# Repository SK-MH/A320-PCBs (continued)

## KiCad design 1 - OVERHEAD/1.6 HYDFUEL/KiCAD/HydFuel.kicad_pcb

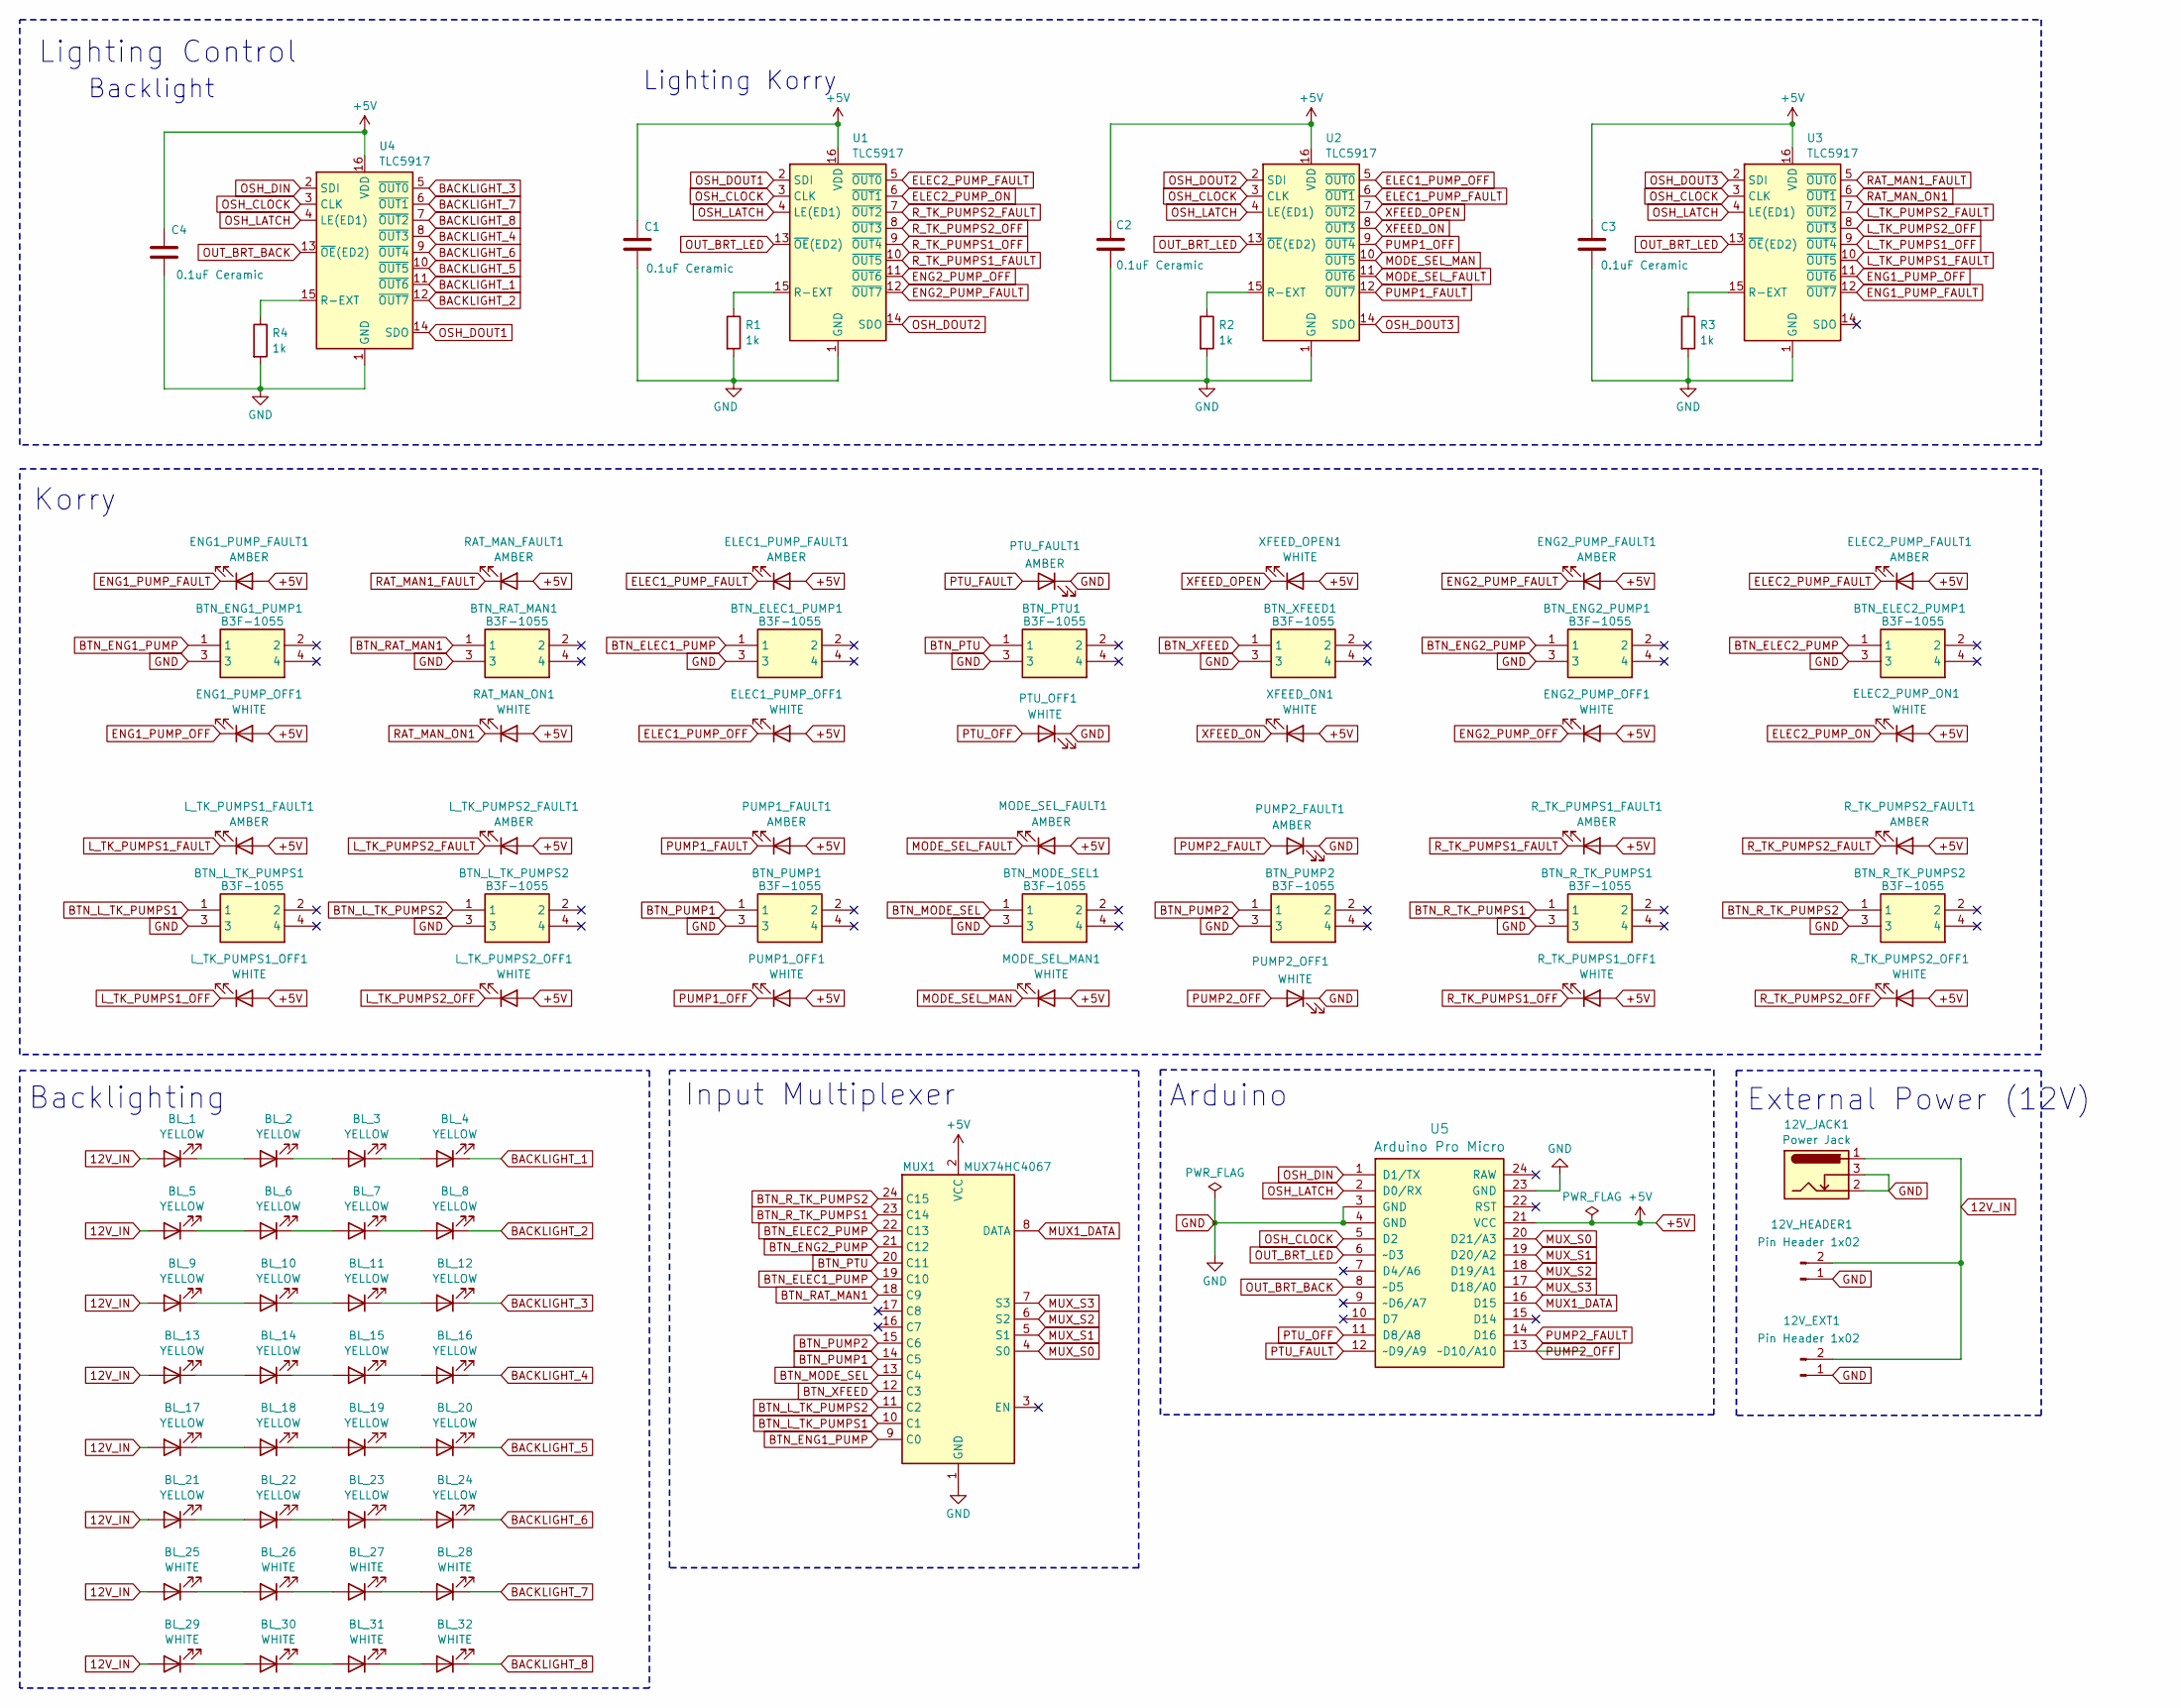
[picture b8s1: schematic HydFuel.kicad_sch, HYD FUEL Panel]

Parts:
12V_EXT1, 12V_HEADER1: Pin Header 1x02; JST_EH_B2B-EH-A_1x02_P2.50mm_Vertical
12V_JACK1: Power Jack; BarrelJack_Horizontal
BL_1, BL_2, BL_3, BL_4, BL_5, BL_6, BL_7, BL_8, BL_9, BL_10, BL_11, BL_12, BL_13, BL_14, BL_15, BL_16, BL_17, BL_18, BL_19, BL_20, BL_21, BL_22, BL_23, BL_24: YELLOW; LED_D3.0mm
BL_25, BL_26, BL_27, BL_28, BL_29, BL_30, BL_31, BL_32: WHITE; LED_D3.0mm
BTN_ELEC1_PUMP1, BTN_ELEC2_PUMP1: B3F-1055; B3F1000; Mouser Part Number 653-B3F-1055
BTN_ENG1_PUMP1, BTN_ENG2_PUMP1: B3F-1055; B3F1000; Mouser Part Number 653-B3F-1055
BTN_L_TK_PUMPS1, BTN_L_TK_PUMPS2: B3F-1055; B3F1000; Mouser Part Number 653-B3F-1055
BTN_MODE_SEL1: B3F-1055; B3F1000; Mouser Part Number 653-B3F-1055
BTN_PTU1: B3F-1055; B3F1000; Mouser Part Number 653-B3F-1055
BTN_PUMP1, BTN_PUMP2: B3F-1055; B3F1000; Mouser Part Number 653-B3F-1055
BTN_RAT_MAN1: B3F-1055; B3F1000; Mouser Part Number 653-B3F-1055
BTN_R_TK_PUMPS1, BTN_R_TK_PUMPS2: B3F-1055; B3F1000; Mouser Part Number 653-B3F-1055
BTN_XFEED1: B3F-1055; B3F1000; Mouser Part Number 653-B3F-1055
C1, C2, C3, C4: 0.1uF Ceramic; C_Disc_D3.0mm_W1.6mm_P2.50mm
ELEC1_PUMP_FAULT1, ELEC2_PUMP_FAULT1: AMBER; LED_D3.0mm
ELEC1_PUMP_OFF1, ELEC2_PUMP_ON1: WHITE; LED_D3.0mm
ENG1_PUMP_FAULT1, ENG2_PUMP_FAULT1: AMBER; LED_D3.0mm
ENG1_PUMP_OFF1, ENG2_PUMP_OFF1: WHITE; LED_D3.0mm
L_TK_PUMPS1_FAULT1, L_TK_PUMPS2_FAULT1: AMBER; LED_D3.0mm
L_TK_PUMPS1_OFF1, L_TK_PUMPS2_OFF1: WHITE; LED_D3.0mm
MODE_SEL_FAULT1: AMBER; LED_D3.0mm
MODE_SEL_MAN1: WHITE; LED_D3.0mm
MUX1: MUX74HC4067
PTU_FAULT1: AMBER; LED_D3.0mm
PTU_OFF1: WHITE; LED_D3.0mm
PUMP1_FAULT1, PUMP2_FAULT1: AMBER; LED_D3.0mm
PUMP1_OFF1, PUMP2_OFF1: WHITE; LED_D3.0mm
R1, R2, R3, R4: 1k; R_Axial_DIN0204_L3.6mm_D1.6mm_P7.62mm_Horizontal
RAT_MAN_FAULT1: AMBER; LED_D3.0mm
RAT_MAN_ON1: WHITE; LED_D3.0mm
R_TK_PUMPS1_FAULT1, R_TK_PUMPS2_FAULT1: AMBER; LED_D3.0mm
R_TK_PUMPS1_OFF1, R_TK_PUMPS2_OFF1: WHITE; LED_D3.0mm
U1, U2, U3, U4: TLC5917; DIP-16_W7.62mm
U5: Arduino Pro Micro; Sparkfun_Pro_Micro
XFEED_ON1: WHITE; LED_D3.0mm
XFEED_OPEN1: WHITE; LED_D3.0mm

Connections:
12V_IN: 12V_EXT1.2, 12V_HEADER1.2, 12V_JACK1.1, BL_1.2 (A), BL_5.2 (A), BL_9.2 (A), BL_13.2 (A), BL_17.2 (A), BL_21.2 (A), BL_25.2 (A), BL_29.2 (A)
+5V: C1.1, C2.1, C3.1, C4.1, ELEC1_PUMP_FAULT1.2 (A), ELEC1_PUMP_OFF1.2 (A), ELEC2_PUMP_FAULT1.2 (A), ELEC2_PUMP_ON1.2 (A), ENG1_PUMP_FAULT1.2 (A), ENG1_PUMP_OFF1.2 (A), ENG2_PUMP_FAULT1.2 (A), ENG2_PUMP_OFF1.2 (A), L_TK_PUMPS1_FAULT1.2 (A), L_TK_PUMPS1_OFF1.2 (A), L_TK_PUMPS2_FAULT1.2 (A), L_TK_PUMPS2_OFF1.2 (A), MODE_SEL_FAULT1.2 (A), MODE_SEL_MAN1.2 (A), MUX1.2 (VCC), PUMP1_FAULT1.2 (A), PUMP1_OFF1.2 (A), RAT_MAN_FAULT1.2 (A), RAT_MAN_ON1.2 (A), R_TK_PUMPS1_FAULT1.2 (A), R_TK_PUMPS1_OFF1.2 (A), R_TK_PUMPS2_FAULT1.2 (A), R_TK_PUMPS2_OFF1.2 (A), U1.16 (VDD), U2.16 (VDD), U3.16 (VDD), U4.16 (VDD), U5.21 (VCC), XFEED_ON1.2 (A), XFEED_OPEN1.2 (A)
BACKLIGHT_1: BL_4.1 (K), U4.11 (~OUT6)
BACKLIGHT_2: BL_8.1 (K), U4.12 (~OUT7)
BACKLIGHT_3: BL_12.1 (K), U4.5 (~OUT0)
BACKLIGHT_4: BL_16.1 (K), U4.8 (~OUT3)
BACKLIGHT_5: BL_20.1 (K), U4.10 (~OUT5)
BACKLIGHT_6: BL_24.1 (K), U4.9 (~OUT4)
BACKLIGHT_7: BL_28.1 (K), U4.6 (~OUT1)
BACKLIGHT_8: BL_32.1 (K), U4.7 (~OUT2)
BTN_ELEC1_PUMP: BTN_ELEC1_PUMP1.1, MUX1.19 (C10)
BTN_ELEC2_PUMP: BTN_ELEC2_PUMP1.1, MUX1.22 (C13)
BTN_ENG1_PUMP: BTN_ENG1_PUMP1.1, MUX1.9 (C0)
BTN_ENG2_PUMP: BTN_ENG2_PUMP1.1, MUX1.21 (C12)
BTN_L_TK_PUMPS1: BTN_L_TK_PUMPS1.1, MUX1.10 (C1)
BTN_L_TK_PUMPS2: BTN_L_TK_PUMPS2.1, MUX1.11 (C2)
BTN_MODE_SEL: BTN_MODE_SEL1.1, MUX1.13 (C4)
BTN_PTU: BTN_PTU1.1, MUX1.20 (C11)
BTN_PUMP1: BTN_PUMP1.1, MUX1.14 (C5)
BTN_PUMP2: BTN_PUMP2.1, MUX1.15 (C6)
BTN_RAT_MAN1: BTN_RAT_MAN1.1, MUX1.18 (C9)
BTN_R_TK_PUMPS1: BTN_R_TK_PUMPS1.1, MUX1.23 (C14)
BTN_R_TK_PUMPS2: BTN_R_TK_PUMPS2.1, MUX1.24 (C15)
BTN_XFEED: BTN_XFEED1.1, MUX1.12 (C3)
ELEC1_PUMP_FAULT: ELEC1_PUMP_FAULT1.1 (K), U2.6 (~OUT1)
ELEC1_PUMP_OFF: ELEC1_PUMP_OFF1.1 (K), U2.5 (~OUT0)
ELEC2_PUMP_FAULT: ELEC2_PUMP_FAULT1.1 (K), U1.5 (~OUT0)
ELEC2_PUMP_ON: ELEC2_PUMP_ON1.1 (K), U1.6 (~OUT1)
ENG1_PUMP_FAULT: ENG1_PUMP_FAULT1.1 (K), U3.12 (~OUT7)
ENG1_PUMP_OFF: ENG1_PUMP_OFF1.1 (K), U3.11 (~OUT6)
ENG2_PUMP_FAULT: ENG2_PUMP_FAULT1.1 (K), U1.12 (~OUT7)
ENG2_PUMP_OFF: ENG2_PUMP_OFF1.1 (K), U1.11 (~OUT6)
GND: 12V_EXT1.1, 12V_HEADER1.1, 12V_JACK1.2, 12V_JACK1.3, BTN_ELEC1_PUMP1.3, BTN_ELEC2_PUMP1.3, BTN_ENG1_PUMP1.3, BTN_ENG2_PUMP1.3, BTN_L_TK_PUMPS1.3, BTN_L_TK_PUMPS2.3, BTN_MODE_SEL1.3, BTN_PTU1.3, BTN_PUMP1.3, BTN_PUMP2.3, BTN_RAT_MAN1.3, BTN_R_TK_PUMPS1.3, BTN_R_TK_PUMPS2.3, BTN_XFEED1.3, C1.2, C2.2, C3.2, C4.2, MUX1.1 (GND), PTU_FAULT1.1 (K), PTU_OFF1.1 (K), PUMP2_FAULT1.1 (K), PUMP2_OFF1.1 (K), R1.2, R2.2, R3.2, R4.2, U1.1 (GND), U2.1 (GND), U3.1 (GND), U4.1 (GND), U5.3 (GND), U5.4 (GND), U5.23 (GND)
L_TK_PUMPS1_FAULT: L_TK_PUMPS1_FAULT1.1 (K), U3.10 (~OUT5)
L_TK_PUMPS1_OFF: L_TK_PUMPS1_OFF1.1 (K), U3.9 (~OUT4)
L_TK_PUMPS2_FAULT: L_TK_PUMPS2_FAULT1.1 (K), U3.7 (~OUT2)
L_TK_PUMPS2_OFF: L_TK_PUMPS2_OFF1.1 (K), U3.8 (~OUT3)
MODE_SEL_FAULT: MODE_SEL_FAULT1.1 (K), U2.11 (~OUT6)
MODE_SEL_MAN: MODE_SEL_MAN1.1 (K), U2.10 (~OUT5)
MUX1_DATA: MUX1.8 (DATA), U5.16 (D15)
MUX_S0: MUX1.4 (S0), U5.20 (D21/A3)
MUX_S1: MUX1.5 (S1), U5.19 (D20/A2)
MUX_S2: MUX1.6 (S2), U5.18 (D19/A1)
MUX_S3: MUX1.7 (S3), U5.17 (D18/A0)
unnamed: BL_1.1 (K), BL_2.2 (A)
unnamed: BL_2.1 (K), BL_3.2 (A)
unnamed: BL_3.1 (K), BL_4.2 (A)
unnamed: BL_5.1 (K), BL_6.2 (A)
unnamed: BL_6.1 (K), BL_7.2 (A)
unnamed: BL_7.1 (K), BL_8.2 (A)
unnamed: BL_9.1 (K), BL_10.2 (A)
unnamed: BL_10.1 (K), BL_11.2 (A)
unnamed: BL_11.1 (K), BL_12.2 (A)
unnamed: BL_13.1 (K), BL_14.2 (A)
unnamed: BL_14.1 (K), BL_15.2 (A)
unnamed: BL_15.1 (K), BL_16.2 (A)
unnamed: BL_17.1 (K), BL_18.2 (A)
unnamed: BL_18.1 (K), BL_19.2 (A)
unnamed: BL_19.1 (K), BL_20.2 (A)
unnamed: BL_21.1 (K), BL_22.2 (A)
unnamed: BL_22.1 (K), BL_23.2 (A)
unnamed: BL_23.1 (K), BL_24.2 (A)
unnamed: BL_25.1 (K), BL_26.2 (A)
unnamed: BL_26.1 (K), BL_27.2 (A)
unnamed: BL_27.1 (K), BL_28.2 (A)
unnamed: BL_29.1 (K), BL_30.2 (A)
unnamed: BL_30.1 (K), BL_31.2 (A)
unnamed: BL_31.1 (K), BL_32.2 (A)
unnamed: R1.1, U1.15 (R-EXT)
unnamed: R2.1, U2.15 (R-EXT)
unnamed: R3.1, U3.15 (R-EXT)
unnamed: R4.1, U4.15 (R-EXT)
OSH_CLOCK: U1.3 (CLK), U2.3 (CLK), U3.3 (CLK), U4.3 (CLK), U5.5 (D2)
OSH_DIN: U4.2 (SDI), U5.1 (D1/TX)
OSH_DOUT1: U1.2 (SDI), U4.14 (SDO)
OSH_DOUT2: U1.14 (SDO), U2.2 (SDI)
OSH_DOUT3: U2.14 (SDO), U3.2 (SDI)
OSH_LATCH: U1.4 (LE(ED1)), U2.4 (LE(ED1)), U3.4 (LE(ED1)), U4.4 (LE(ED1)), U5.2 (D0/RX)
OUT_BRT_BACK: U4.13 (~OE(ED2)), U5.8 (~D5)
OUT_BRT_LED: U1.13 (~OE(ED2)), U2.13 (~OE(ED2)), U3.13 (~OE(ED2)), U5.6 (~D3)
PTU_FAULT: PTU_FAULT1.2 (A), U5.12 (~D9/A9)
PTU_OFF: PTU_OFF1.2 (A), U5.11 (D8/A8)
PUMP1_FAULT: PUMP1_FAULT1.1 (K), U2.12 (~OUT7)
PUMP1_OFF: PUMP1_OFF1.1 (K), U2.9 (~OUT4)
PUMP2_FAULT: PUMP2_FAULT1.2 (A), U5.14 (D16)
PUMP2_OFF: PUMP2_OFF1.2 (A), U5.13 (~D10/A10)
RAT_MAN1_FAULT: RAT_MAN_FAULT1.1 (K), U3.5 (~OUT0)
RAT_MAN_ON1: RAT_MAN_ON1.1 (K), U3.6 (~OUT1)
R_TK_PUMPS1_FAULT: R_TK_PUMPS1_FAULT1.1 (K), U1.10 (~OUT5)
R_TK_PUMPS1_OFF: R_TK_PUMPS1_OFF1.1 (K), U1.9 (~OUT4)
R_TK_PUMPS2_FAULT: R_TK_PUMPS2_FAULT1.1 (K), U1.7 (~OUT2)
R_TK_PUMPS2_OFF: R_TK_PUMPS2_OFF1.1 (K), U1.8 (~OUT3)
XFEED_ON: U2.8 (~OUT3), XFEED_ON1.1 (K)
XFEED_OPEN: U2.7 (~OUT2), XFEED_OPEN1.1 (K)

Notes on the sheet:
Backlighting
Arduino
Korry
Input Multiplexer
External Power (12V)
Lighting Korry
Lighting Control
Backlight

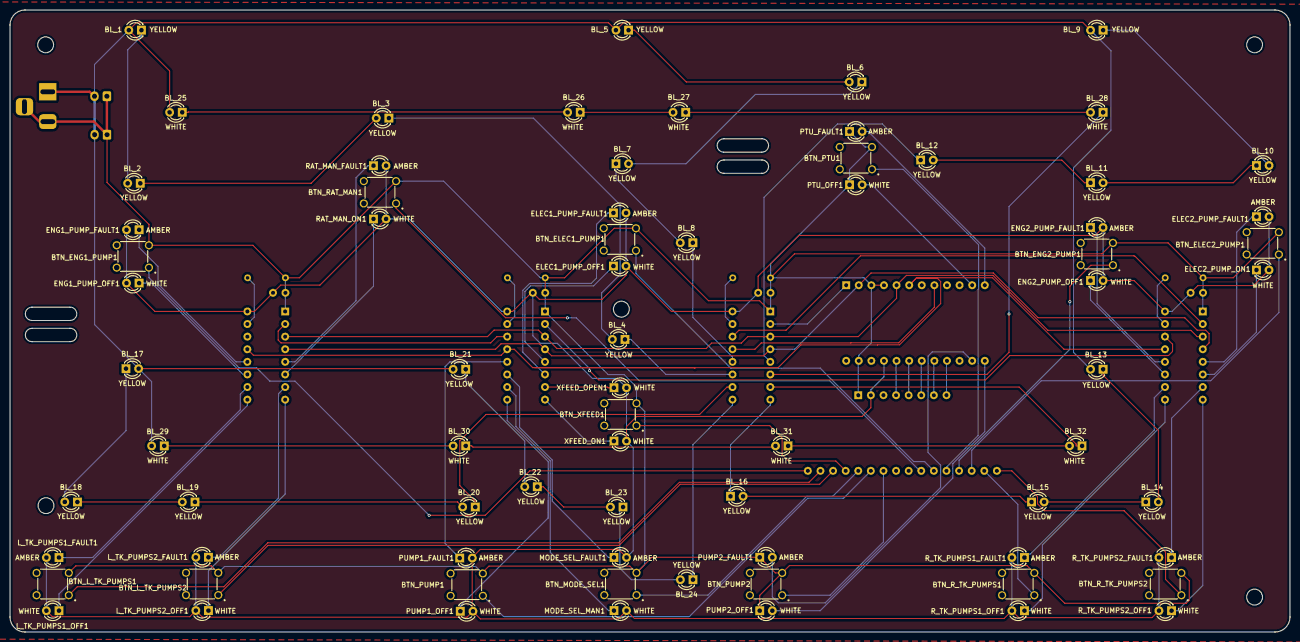
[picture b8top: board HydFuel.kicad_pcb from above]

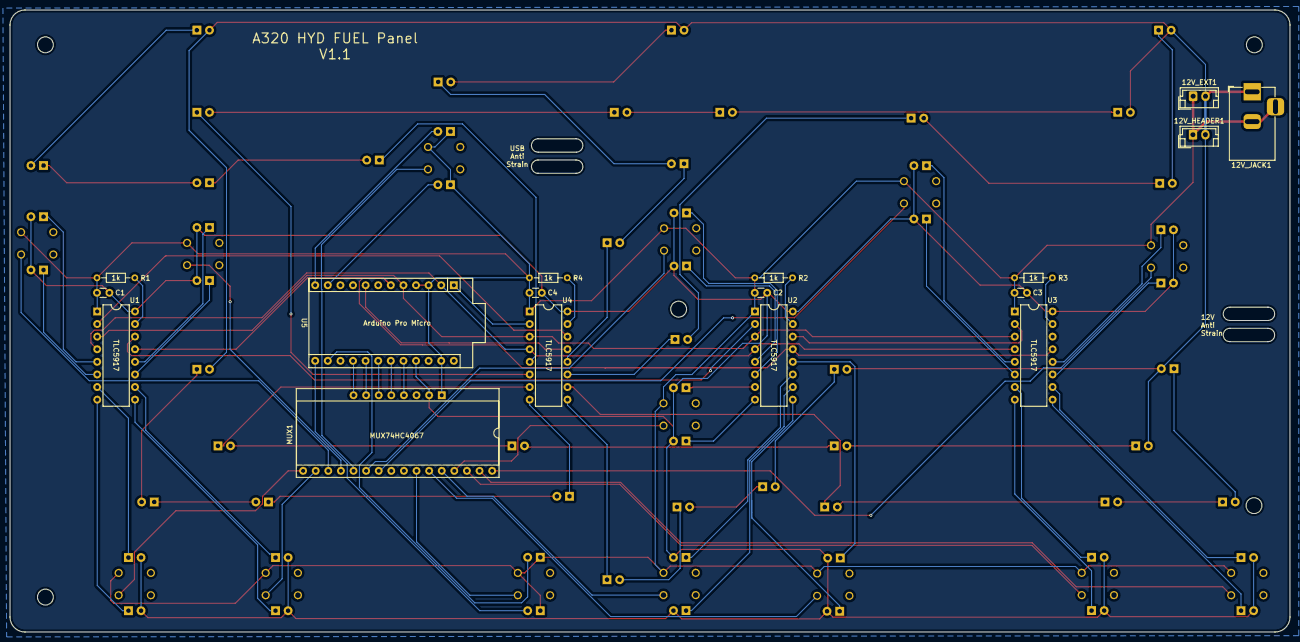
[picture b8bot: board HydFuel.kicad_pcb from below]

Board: 2 copper layers, 258.0 x 125.4 mm, 91 parts (17 on the bottom side), 94 nets.

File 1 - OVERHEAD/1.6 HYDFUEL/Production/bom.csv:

Designator,Footprint,Quantity,Value,LCSC Part #
"12V_EXT1, 12V_HEADER1",JST_EH_B2B-EH-A_1x02_P2.50mm_Vertical,2,Pin Header 1x02,
12V_JACK1,BarrelJack_Horizontal,1,Power Jack,
"BL_1, BL_10, BL_11, BL_12, BL_13, BL_14, BL_15, BL_16, BL_17, BL_18, BL_19, BL_2, BL_20, BL_21, BL_22, BL_23, BL_24, BL_3, BL_4, BL_5, BL_6, BL_7, BL_8, BL_9",LED_D3.0mm,24,YELLOW,
"BL_25, BL_26, BL_27, BL_28, BL_29, BL_30, BL_31, BL_32, ELEC1_PUMP_OFF1, ELEC2_PUMP_ON1, ENG1_PUMP_OFF1, ENG2_PUMP_OFF1, L_TK_PUMPS1_OFF1, L_TK_PUMPS2_OFF1, MODE_SEL_MAN1, PTU_OFF1, PUMP1_OFF1, PUMP2_OFF1, RAT_MAN_ON1, R_TK_PUMPS1_OFF1, R_TK_PUMPS2_OFF1, XFEED_ON1, XFEED_OPEN1",LED_D3.0mm,23,WHITE,
"BTN_ELEC1_PUMP1, BTN_ELEC2_PUMP1, BTN_ENG1_PUMP1, BTN_ENG2_PUMP1, BTN_L_TK_PUMPS1, BTN_L_TK_PUMPS2, BTN_MODE_SEL1, BTN_PTU1, BTN_PUMP1, BTN_PUMP2, BTN_RAT_MAN1, BTN_R_TK_PUMPS1, BTN_R_TK_PUMPS2, BTN_XFEED1",B3F1000,14,B3F-1055,
"C1, C2, C3, C4",C_Disc_D3.0mm_W1.6mm_P2.50mm,4,0.1uF Ceramic,
"ELEC1_PUMP_FAULT1, ELEC2_PUMP_FAULT1, ENG1_PUMP_FAULT1, ENG2_PUMP_FAULT1, L_TK_PUMPS1_FAULT1, L_TK_PUMPS2_FAULT1, MODE_SEL_FAULT1, PTU_FAULT1, PUMP1_FAULT1, PUMP2_FAULT1, RAT_MAN_FAULT1, R_TK_PUMPS1_FAULT1, R_TK_PUMPS2_FAULT1",LED_D3.0mm,13,AMBER,
MUX1,MUX74HC4067,1,MUX74HC4067,
"R1, R2, R3, R4",R_Axial_DIN0204_L3.6mm_D1.6mm_P7.62mm_Horizontal,4,1k,
"U1, U2, U3, U4",DIP-16_W7.62mm,4,TLC5917,
U5,Sparkfun_Pro_Micro,1,Arduino Pro Micro,
